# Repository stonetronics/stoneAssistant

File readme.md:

stoneAssistant

This repository contains (pcb, firmware, mechanical) design files for the stoneAssistant project.
The stoneAssistant is meant to be a home-entertainment device built around a raspberry pi.

Planned features:
 - Raspberry Pi 3
 - LCD Touch Screen (official Raspberry Pi Touch Screen)
 - 15W Stereo sound
 - 12V Supply
 - 3 USB Ports
 - Speech Commands
   - microphone preamp
 - Pushbuttons for optional control (Home button, Play/Pause, etc)
 - ATtiny
   - RGB LED for nice appearance
   - Shutdown and Power Control
   - Controlable Fan
   - Serial Commands
 - 3D-printed enclosure
 
The device is powered by a 230VAC/12VDC switching supply and another 12VDC/5VDC DC/DC converter that powers the Raspberry Pi, ATtiny and USB Ports.
For power control (5V on Raspberry Pi, Software controlable mains switch), fan control and the RGB LEDs an ATtiny2312 chip is used. The chip implements a serial command interface on the uart to talk to the Raspberry Pi and vice versa.
The software (RingoWare) for touch screen control, media, etc is currently developed by https://github.com/Ringo96 and there will be a repo by him soon.
All the mechanical design files are drawn in FreeCAD 0.16. All the screw holes are designed to work with M3 screws. The PCBs sitting on top of the raspberry pi are meant to be held in place by standard M3 PCB spacers.

Files:

PCB files (Eagle 8)
- /PCBs/stoneAssistant_pwrMgmt.sch Power management and pwm schematic
- /PCBs/stoneAssistant_pwrMgmt.brd Power management and pwm board

Firmware files (Atmel Studio 7)
- /ATtinyFirmware/stoneAssistantController		Atmel Studio Solution for the ATtiny on the pwrMgmt board
 
Mechanical files (FreeCAD 0.16)
- /Mechanical/buttonPrototype    Prototype for Button with stopper
- /Mechanical/Frontplate         Frontplate that holds the raspberry pi display, buttons and speakers - prototype, did not fit in 3d printer
- /Mechanical/RPIMount           Mounting that holds the raspberry pi + PCBs on the raspberry pi display
- /Mechanical/Housing			 Model of the housing
!!!!!Moved all mechanical files to thingiverse

Serial Command Interface:

The serial command interface is using the uart and is based on a simple protocol, described below:

1 packet:
[Startbyte(0xaa)][Length][payload 0][payload 1] ... payload[length - 1][Stopbyte(0x55)]

In the payload of this protocol, the commands are transmitted. The following commands are implemented:
- [R][x] set red led intensity to x (0-255) (rpi->attiny)
- [G][x] set green led intensity to x (0-255) (rpi->attiny)
- [B][x] set blue led intensity to x (0-255) (rpi->attiny)
- [F][x] set fan speed to x (0-255) (rpi->attiny)
- [C][0] shutdown in 15s (rpi->attiny)
- [C][1] shutdown request (attiny->rpi)
- [C][6] cut rpi power and turn it on again in 15s (rpi->attiny)
- [C][9] hard reset rpi immediately (rpi->attiny)
- [C][10] hard shutdown immediately (rpi->attiny)

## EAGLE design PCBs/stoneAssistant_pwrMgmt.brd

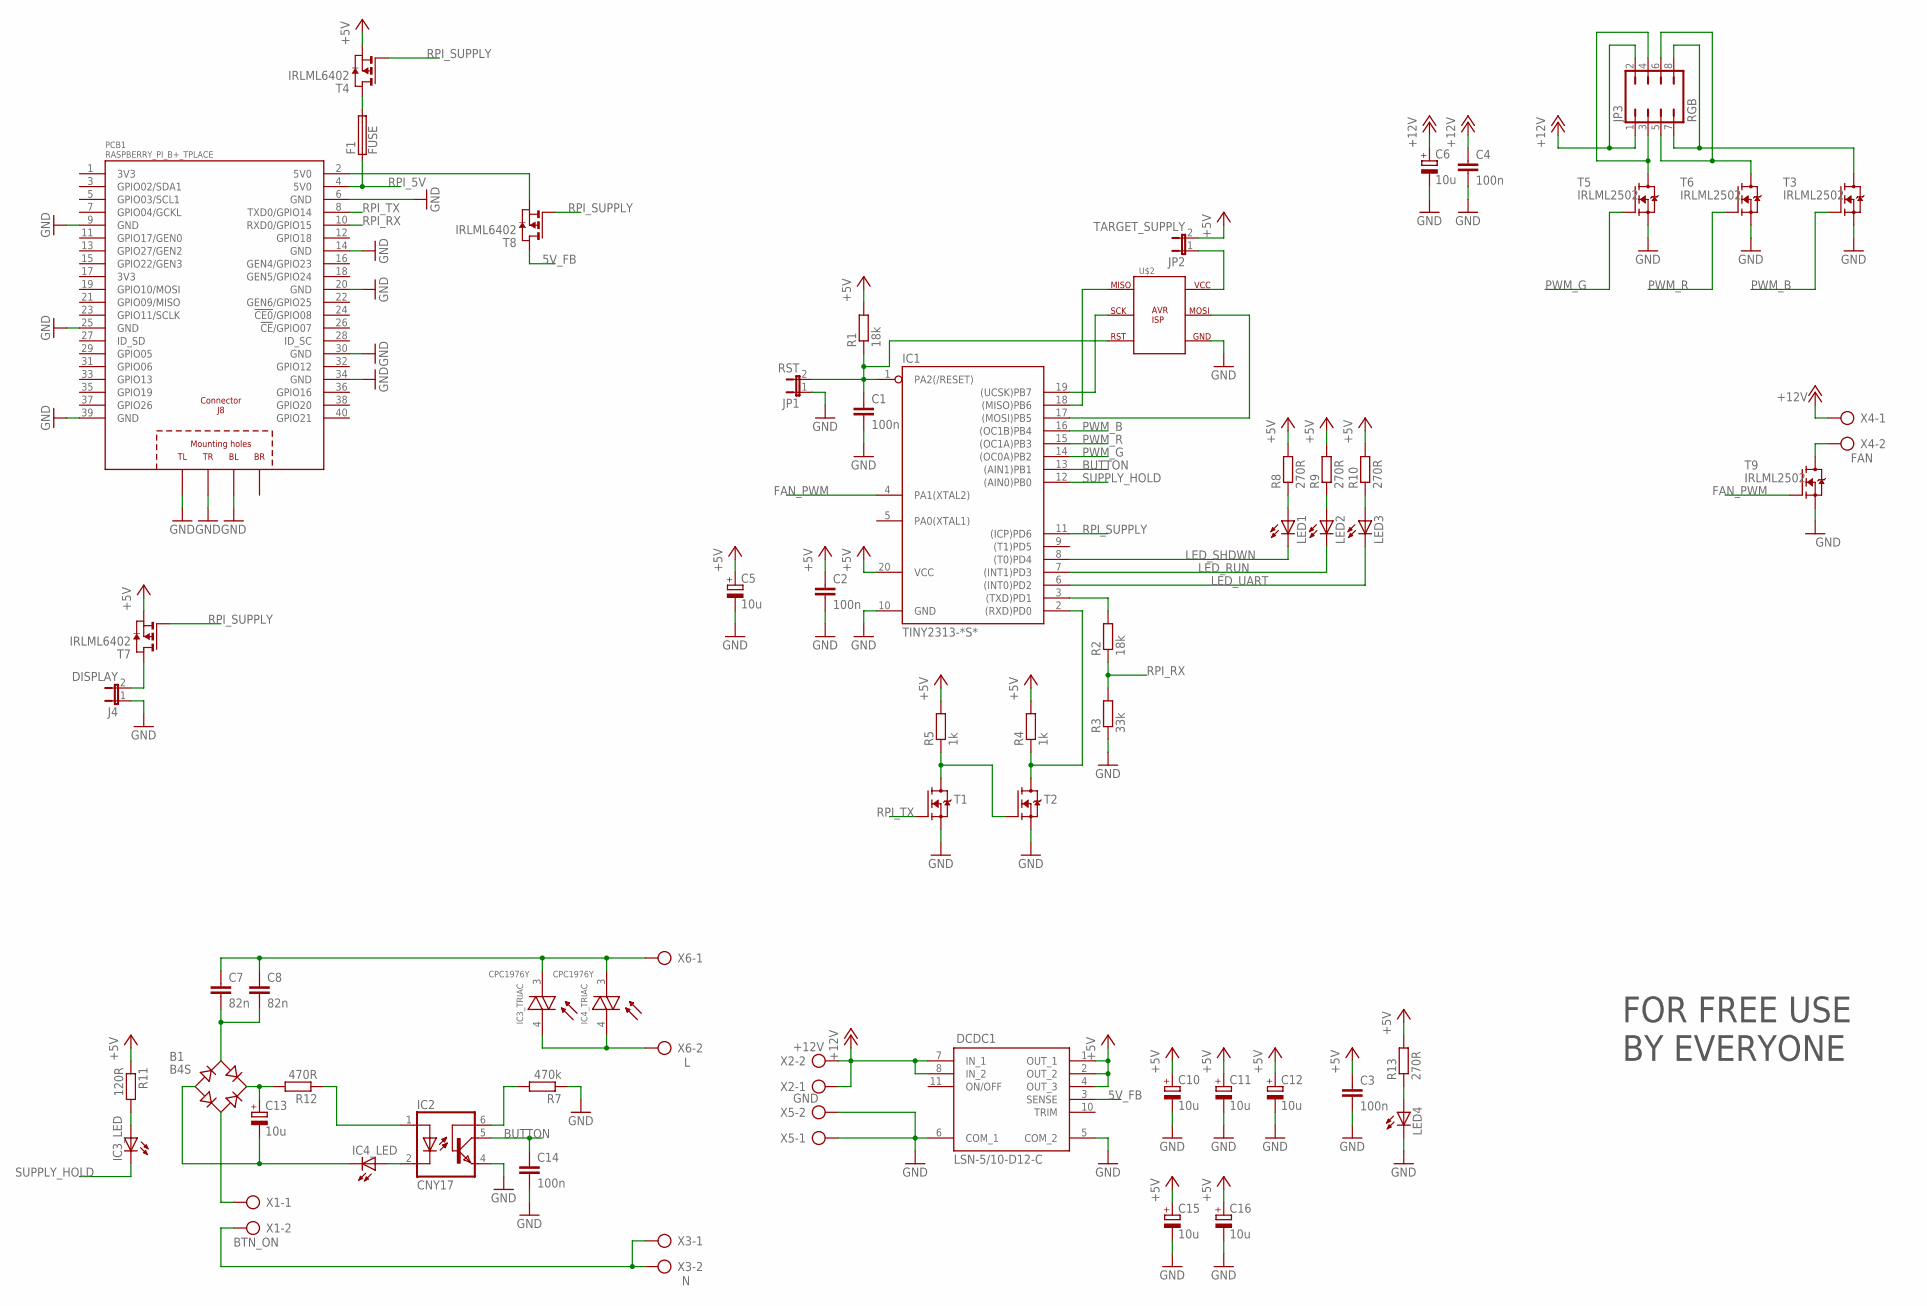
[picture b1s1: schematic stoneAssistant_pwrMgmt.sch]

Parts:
B1: B4S; MBS
C1, C2, C3, C4, C14: 100n; C0805
C5, C6, C10, C11, C12, C13, C15, C16: 10u; SMC_A
C7, C8: 82n; C050-075X075
DCDC1: LSN-5/10-D12-C; MURATA_LSN-5/10-D12-C
F1: FUSE; MF-SMDF050
IC1: TINY2313-*S*; SO20L$
IC2: CNY17; DIL06
IC3, IC4: CPC1976Y; SIP8/4
J4: DISPLAY; JP1
JP1: RST; JP1
JP2: TARGET_SUPPLY; JP1
JP3: RGB; JP4Q
LED1, LED2, LED3, LED4: LEDCHIPLED_0805; CHIPLED_0805
PCB1: RASPBERRY_PI_B+_TPLACE; RASPBERRY_PI_BPLUS_TPLACE
R1, R2: 18k; M0805
R3: 33k; M0805
R4, R5: 1k; M0805
R7: 470k; M0805
R8, R9, R10, R13: 270R; M0805
R11: 120R; M0805
R12: 470R; M0805
T1, T2: MOSFET-N-SOT23; SOT23
T3, T5, T6, T9: IRLML2502; SOT-23
T4, T7, T8: IRLML6402; SOT-23
U$2: AVR_ISPSINGLESIDED_SMD; PINHEADER_254_2X3_SMD
X1: BTN_ON; 2_2.54MM
X2: +12V; 2_2.54MM
X3: N; 2_2.54MM
X4: FAN; 2_2.54MM
X5: GND; 2_2.54MM
X6: L; 2_2.54MM

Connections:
3V3: PCB1.1 (3V3), PCB1.17 (3V3)
5V_FB: DCDC1.3 (SENSE), T8.3 (D)
+5V: C2.1, C3.1, C5.+, C10.+, C11.+, C12.+, C15.+, C16.+, DCDC1.1 (OUT_1), DCDC1.2 (OUT_2), DCDC1.4 (OUT_3), IC1.20 (VCC), JP2.2, R1.2, R4.2, R5.2, R8.2, R9.2, R10.2, R11.1, R13.2, T4.2 (S), T7.2 (S)
+12V: C4.1, C6.+, DCDC1.7 (IN_1), DCDC1.8 (IN_2), JP3.1, JP3.2, X2.1, X2.2, X4.1
BUTTON: C14.1, IC1.13 ((AIN1)PB1), IC2.5 (COL)
FAN_PWM: IC1.4 (PA1(XTAL2)), T9.1 (G)
GND: C1.2, C2.2, C3.2, C4.2, C5.-, C6.-, C10.-, C11.-, C12.-, C14.2, C15.-, C16.-, DCDC1.5 (COM_2), DCDC1.6 (COM_1), IC1.10 (GND), IC2.4 (EMI), J4.1, JP1.1, LED4.C, PCB1.6 (GND), PCB1.9 (GND), PCB1.14 (GND), PCB1.20 (GND), PCB1.25 (GND), PCB1.30 (GND), PCB1.34 (GND), PCB1.39 (GND), PCB1.PE_BL (BL), PCB1.PE_TL (TL), PCB1.PE_TR (TR), R3.1, R7.1, T1.2 (S), T2.2 (S), T3.2 (S), T5.2 (S), T6.2 (S), T9.2 (S), U$2.P$6 (GND), X5.1, X5.2
LED_RUN: IC1.7 ((INT1)PD3), LED2.C
LED_SHDWN: IC1.8 ((T0)PD4), LED1.C
LED_UART: IC1.6 ((INT0)PD2), LED3.C
unnamed: C1.1, IC1.1 (PA2(/RESET)), JP1.2, R1.1, U$2.P$3 (RST)
unnamed: IC1.3 ((TXD)PD1), R2.2
unnamed: IC1.2 ((RXD)PD0), R4.1, T2.3 (D)
unnamed: R5.1, T1.3 (D), T2.1 (G)
unnamed: IC2.2 (C), IC4.2 (A)
unnamed: IC1.19 ((UCSK)PB7), U$2.P$2 (SCK)
unnamed: IC1.18 ((MISO)PB6), U$2.P$1 (MISO)
unnamed: IC1.17 ((MOSI)PB5), U$2.P$7 (MOSI)
unnamed: JP2.1, U$2.P$8 (VCC)
unnamed: IC3.4 (A/C2), IC4.4 (A/C2), X6.2
unnamed: C7.1, C8.1, IC3.3 (A/C1), IC4.3 (A/C1), X6.1
unnamed: X1.2, X3.1, X3.2
unnamed: B1.AC1, C7.2, C8.2
unnamed: B1.-, C13.-, IC4.1 (C)
unnamed: B1.+, C13.+, R12.2
unnamed: B1.AC2, X1.1
unnamed: IC2.1 (A), R12.1
unnamed: IC2.6 (BAS), R7.2
unnamed: F1.2, T4.3 (D)
unnamed: LED4.A, R13.1
unnamed: JP3.3, JP3.4, T5.3 (D)
unnamed: JP3.5, JP3.6, T6.3 (D)
unnamed: JP3.7, JP3.8, T3.3 (D)
unnamed: J4.2, T7.3 (D)
unnamed: T9.3 (D), X4.2
unnamed: IC3.2 (A), R11.2
unnamed: PCB1.2 (5V0), T8.2 (S)
unnamed: LED1.A, R8.1
unnamed: LED2.A, R9.1
unnamed: LED3.A, R10.1
PWM_B: IC1.16 ((OC1B)PB4), T3.1 (G)
PWM_G: IC1.14 ((OC0A)PB2), T5.1 (G)
PWM_R: IC1.15 ((OC1A)PB3), T6.1 (G)
RPI_5V: F1.1, PCB1.4 (5V0)
RPI_RX: PCB1.10 (RXD0/GPIO15), R2.1, R3.2
RPI_SUPPLY: IC1.11 ((ICP)PD6), T4.1 (G), T7.1 (G), T8.1 (G)
RPI_TX: PCB1.8 (TXD0/GPIO14), T1.1 (G)
SUPPLY_HOLD: IC1.12 ((AIN0)PB0), IC3.1 (C)

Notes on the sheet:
FOR FREE USE BY EVERYONE

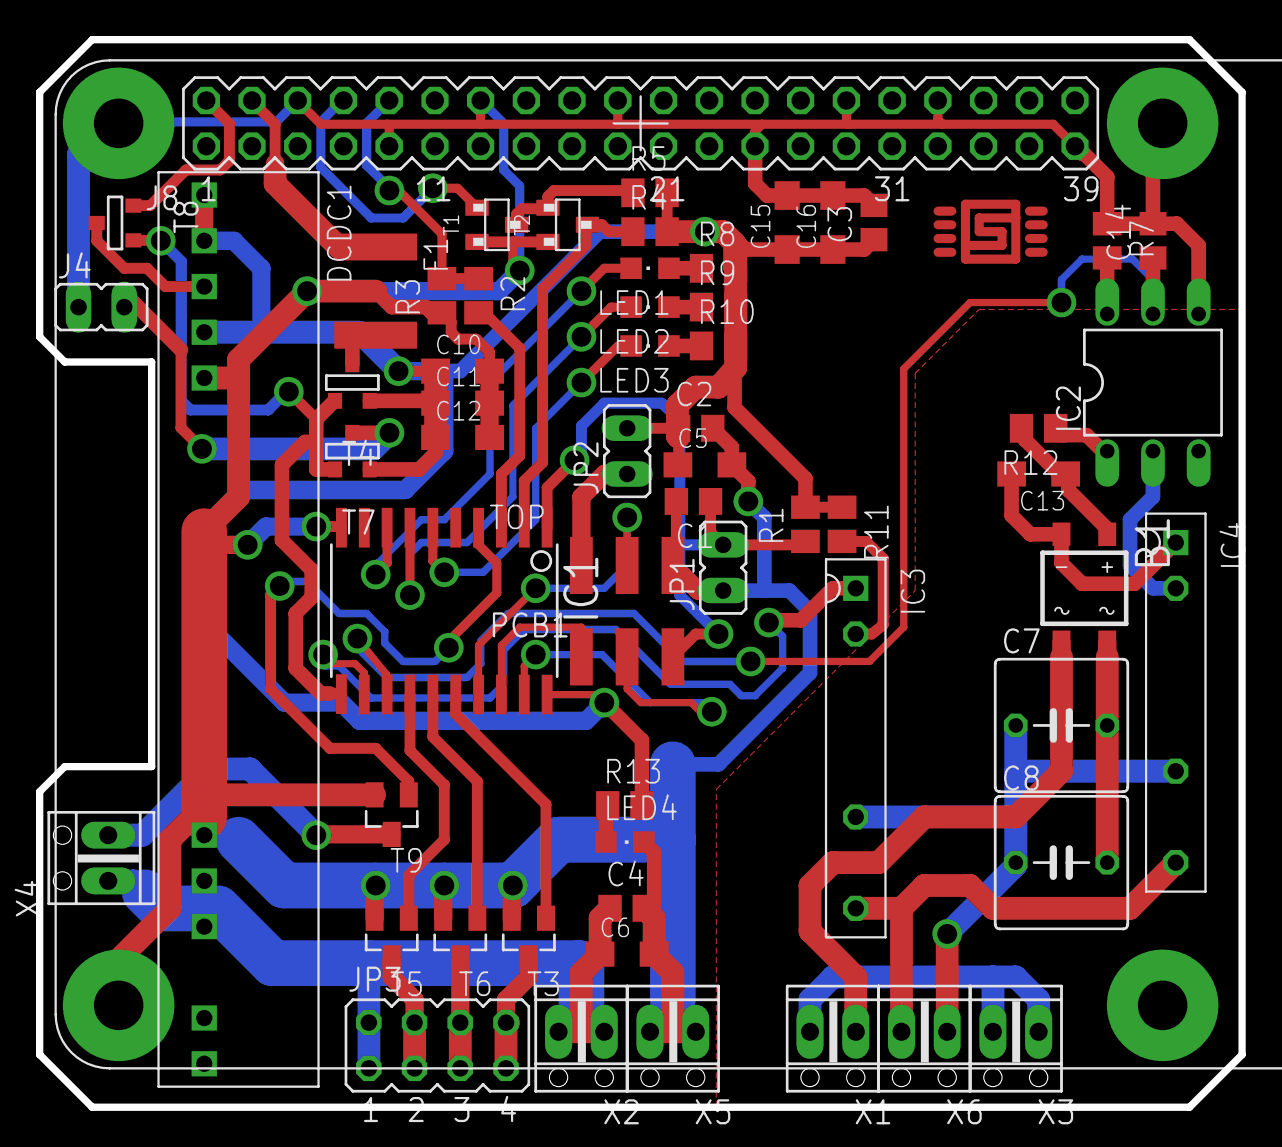
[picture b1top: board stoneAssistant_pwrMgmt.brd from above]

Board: 2 copper layers, 66.8 x 59.3 mm, 59 parts (0 on the bottom side), 48 nets.

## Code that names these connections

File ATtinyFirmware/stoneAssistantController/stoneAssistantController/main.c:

/*
 * stoneAssistantController.c
 *
 * Created: 05.03.2018 16:05:19
 * Author : Stone
 */ 

#define F_CPU  8000000UL

#include <avr/io.h>
#include <avr/interrupt.h>
#include <util/delay.h>
#include <stdlib.h>


#include "rgbPwmTimerFan.h"
#include "uart.h"
#include "stoneProtocol.h"

//time in seconds to give the rpi to shutdown
#define RPI_SHUTDOWN_SECONDS	15

//time in seconds for button press to send soft shutdown request
#define RPI_SHUTDOWN_REQ_TIME	2

//time in seconds for button press to trigger hard shutdown
#define RPI_SHUTDOWN_HARD_TIME	10


#define DDR_LED		DDRD
#define PORT_LED	PORTD
#define LED_SHDWN   PD4
#define LED_RUN		PD3
#define LED_UART    PD2

#define DDR_HOLD	DDRB
#define PORT_HOLD	PORTB
#define PIN_HOLD	PB0

#define DDR_BUTTON	DDRB
#define PORT_BUTTON PORTB
#define PIN_BUTTON	PINB
#define BUTTON		PB1

#define DDR_RPISUP	DDRD
#define PORT_RPISUP	PORTD
#define RPISUP		PD6

void shutdown(uint8_t shutdownSeconds)
{
	uint8_t i = 0; //iteration variable

	PORT_LED &= ~(1<<LED_SHDWN);
	rgbPwm_setHexColor(0x00FF0000); //red light to indicate shutdown sequence has started

	for (i = 0; i < shutdownSeconds; i++)	//shutdown delay
		_delay_ms(1000);

	PORT_RPISUP |= 1<<RPISUP; //release raspberry pi power supply
	PORT_HOLD |= 1<<PIN_HOLD; //release mains power supply (turn off)
}

void rpiHardReset(uint8_t shutdownSeconds)
{
	uint8_t i = 0; //iteration variable

	rgbPwm_setHexColor(0x00fffb26); //yellow light to indicate hard reset sequence has started

	for (i = 0; i < shutdownSeconds; i++)	//shutdown delay
		_delay_ms(1000);

	PORT_RPISUP |= 1<<RPISUP; //release raspberry pi power supply
	_delay_ms(500); //wait half a second to let the pi "cool down"
	PORT_RPISUP &= ~(1<<RPISUP); //turn on rpi power supply

	rgbPwm_setHexColor(0x00fffb26); //green light to indicate hard reset sequence has completed, rpi is on power again
}

void shutdownRequest()
{
	uint8_t requestMessage[2];

	requestMessage[0] = 'C';	//control message
	requestMessage[1] = 1;		//shutdown request

	stoneProtocol_transmit(requestMessage, 2);
}

int main(void)
{
	uint8_t inputChar = 0;
	uint8_t* payload = NULL;
	uint8_t protocolRet = 0;

	uint8_t button = 0;
	uint8_t buttonOld = 0;

	//init supply holding circuit (turned on)
	DDR_HOLD |= 1<<PIN_HOLD;
	PORT_HOLD &= ~(1<<PIN_HOLD);

	//init raspberry pi power control (turned on)
	DDR_RPISUP |= 1<<RPISUP;
	PORT_RPISUP &= ~(1<<RPISUP);

	//init button input with internal pull up enabled
	DDR_BUTTON &= ~(1<<BUTTON);
	PORT_BUTTON |= 1<<BUTTON;
	button = PIN_BUTTON & (1<<BUTTON);
	buttonOld = button;

	//init rgb and fan pwm timers (color: indigo, fan: 50%)
	rgbPwmTimerFan_init();
	rgbPwm_setHexColor(0);//x00b522f9);
	fan_setSpeed(127);

	//init leds
	DDR_LED  |= (1<<LED_SHDWN) | (1<<LED_RUN) | (1<<LED_UART);
	PORT_LED |= (1<<LED_SHDWN) | (1<<LED_RUN) | (1<<LED_UART);
	
	//init uart
	uart_init(9600,1,1);
	//init serial protocol
	stoneProtocol_init();

	//enable interrupts (needed for timer stuff)
	sei();

    while (1) 
    {
		//alive indication
		PORT_LED ^= (1<<LED_RUN);

		//button press handling
		button = PIN_BUTTON & (1<<BUTTON);
		if (buttonOld != button)
		{
			buttonOld = button;
			if (!button) //falling edge
			{
				timer_start();
			}
			else //rising edge
			{
				timer_stop();
			}
		}

		//button timer handling for shutdown
		if (timer_getTime() >= RPI_SHUTDOWN_REQ_TIME)
		{
			shutdownRequest();
		}
		if (timer_getTime() >= RPI_SHUTDOWN_HARD_TIME)
		{
			shutdown(1);
		}

		//usart protocol handling, command execution
		if (uart_testAndGetC(&inputChar))
		{
			PORT_LED ^= (1<<LED_UART);

			protocolRet = (stoneProtocol_loop(inputChar));
			switch (protocolRet)
			{
				case 0: //no new packet
				break;

				case 1: //new packet received
					payload = stoneProtocol_getMessage();
					if (payload != NULL)
					{
						switch (payload[0])
						{
							case 'r': //red led pwm - tested
							case 'R':
								rgbPwm_setR(payload[1]);
							break;

							case 'g': //green led pwm - tested
							case 'G':
								rgbPwm_setG(payload[1]);
							break;

							case 'b': //blue led pwm - tested
							case 'B':
								rgbPwm_setB(payload[1]);
							break;

							case 'x': //hexcode color - tested
							case 'X':
								rgbPwm_setHexColor(((uint32_t)payload[1]<<16) | ((uint32_t)payload[2]<<8) | ((uint32_t)payload[3])); //0x00RRGGBB
							break;

							case 'f': //fan pwm - tested
							case 'F':
								fan_setSpeed(payload[1]);
							break;

							case 'c': //command
							case 'C':

								switch (payload[1])
								{
									case 0: //shutdown
										shutdown(RPI_SHUTDOWN_SECONDS);
									break;

									//case 1: //shutdown request - nothing to do on attiny, just here for protocol doc
									//break;

									case 6: //reboot
										rpiHardReset(RPI_SHUTDOWN_SECONDS);
									break;

									case 9: //hard reset
										rpiHardReset(0);
									break;

									case 10: //hard shutdown
										shutdown(0);
									break;

									default:
									break;
								}
							break;

							default:
							break;
						}
						free(payload);
					}
				break;

				case 2: //protocol error
					PORT_LED |= 1<<LED_UART;
				break;
			}
		}
    }
}

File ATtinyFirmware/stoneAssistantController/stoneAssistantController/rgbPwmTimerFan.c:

/*
 * rgbPwm.c
 *
 * Created: 05.03.2018 16:06:15
 *  Author: Stone
 */ 

 #include <avr/io.h>
 #include <avr/interrupt.h>
 #include "rgbPwmTimerFan.h"


 #define DDR_PWM	DDRB
 #define PORT_PWM	PORTB
 #define PIN_PWMB	PB4
 #define PIN_PWMR	PB3
 #define PIN_PWMG	PB2

 #define DDR_FAN		DDRA
 #define PORT_FAN	PORTA
 #define PIN_FAN		PINA
 #define FAN_PWM		PA1
 #define FAN_SIGNAL	PA0

 volatile uint8_t timerRunning;
 volatile uint16_t hundretMsCounter;
 volatile uint16_t overflowCounter;
 volatile uint8_t overflowFlag;

 void rgbPwmTimerFan_init() {
	timerRunning = 0;
	hundretMsCounter = 0;
	overflowCounter = 0;
	overflowFlag = 0;

	//init rgb pwm channel output pins (turned off)
	DDR_PWM |= (1<<PIN_PWMR) | (1<<PIN_PWMG) | (1<<PIN_PWMB);
	PORT_PWM &= ~((1<<PIN_PWMR) | (1<<PIN_PWMG) | (1<<PIN_PWMB));

	//init fan control pins (fan turned off)
	DDR_FAN |= 1<<FAN_PWM;
	PORT_FAN &= ~(1<<FAN_PWM);
	DDR_FAN &= ~(1<<FAN_SIGNAL);
	//PORT_FAN |= (1<<FAN_SIGNAL);

	//timer 0 initialization G - OC0A; interrupt used for Fan - OCR0B; also used for 100ms increment
	TCCR0A |= (2<<COM0A0) | (3<<WGM00); //Fast PWM mode with oc0a = 1 at TCNT0 < OCR0A
	TCCR0B |= (4<<CS00); //start timer with clk/256 = 31.25kHz
	TIMSK |= (1<<OCIE0B) | (1<<TOIE0); //enable interrupts for ocr0b and overflow
	TCNT0 = 0;
	OCR0A = 0;
	OCR0B = 0;

	//timer 1 initialization R - OC1A; B - OC1B;
	TCCR1A |= (2<<COM1A0) | (2<<COM1B0) | (1<<WGM10); //8-Bit Fast PWM with oc1a and oc1b pwm operation
	TCCR1B |= (1<<WGM12) | (4<<CS10); //start timer with clk/256 = 31.25kHz
	TCNT1H = 0;
	TCNT1L = 0;
	OCR1AH = 0;
	OCR1AL = 0;
	OCR1BH = 0;
	OCR1BL = 0;
 }

 void rgbPwm_setR(uint8_t r)
 {
	OCR1AL = r;
 }

 void rgbPwm_setG(uint8_t g)
 {
	OCR0A = g;
 }

 void rgbPwm_setB(uint8_t b)
 {
	OCR1BL = b;
 }

 void rgbPwm_setHexColor(uint32_t hexCode)
 {
	rgbPwm_setR((hexCode & 0x00FF0000)>>16);
	rgbPwm_setG((hexCode & 0x0000FF00)>>8);
	rgbPwm_setB((hexCode & 0x000000FF));
 }

 void fan_setSpeed(uint8_t f)
 {
	OCR0B = f;
 }

 void timer_start()
 {
	uint8_t temp_SREG = 0;

	temp_SREG = SREG;

	cli();

	hundretMsCounter = 0;
	overflowCounter = 0;
	overflowFlag = 0;
	timerRunning = 1;

	SREG = temp_SREG;
 }

 void timer_stop()
 {
	timerRunning = 0;
 }

 uint8_t timer_overflow()
 {
	return overflowFlag;
 }

 uint16_t timer_getTime()
 {
	return hundretMsCounter;
 }

 ISR(TIMER0_COMPB_vect)
 {
	PORT_FAN &= ~(1<<FAN_PWM); //set fan pin low at end of pulse
 }

 ISR(TIMER0_OVF_vect)
 {
	PORT_FAN |= (1<<FAN_PWM); //set fan pin high at start of pulse

	if (timerRunning) //increment timer if enabled
	{
		//counter for 1s
		if ((overflowCounter++) == 122) //999,424ms
		{
			overflowCounter = 0;

			//100ms chunks counter
			if ((hundretMsCounter++) == 0xFFFF)
			{
				hundretMsCounter = 0;
				overflowFlag = 1;
			}
		}
	}
 }

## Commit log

2018-02-21 first prototype for buttons with stopper mechanism included
2018-02-22 lower profile design converted stoppers into linear translation guides adjusted stoppers and pcb mount to 2.54 grid for easier assembly with protoboard strengthening against bending in the front plate
2018-02-23 Refactoring
2018-02-26 Added PCB for power management and pwm Added First Frontplate design with three buttons, display, 2 speakers and usb soundcard pcb holder - seems to be too big for 3d printer, i might redo this so it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
2018-03-12 updated frontplate design -> too big for 3d printer partial case design with tilted speakers button update Raspberry Pi Mounting frame
2018-03-13 mechanical: added first housing design - now fits into printing space
2018-03-13 electrical: pcb redesign for better fit of components, transistor level shifter moved away from dc/dc, smd rectifier instead of tht one, cancelled out snubber, isp moved away from edge so the attiny 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
2018-03-13 firmware: initial firmware commit, includes uart receive protocol handling (tx not tested yet!), pwm on rgb leds, fan pwm still missing, first shutdown functionality
2018-03-15 added fan control and button handling (hard-/soft-shutdown) to the firmware update readme.md
2018-06-14 final power management pcb
2019-03-29 move mechanical to thingiverse
